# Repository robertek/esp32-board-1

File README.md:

# esp32-board-1
Simple ESP32 board design.

Features:
 * 1S lipo battery power
 * battery charger through microUSB
 * UART header for programming
 * I2C header for peripheral
 * battery monitoring throuh ADC

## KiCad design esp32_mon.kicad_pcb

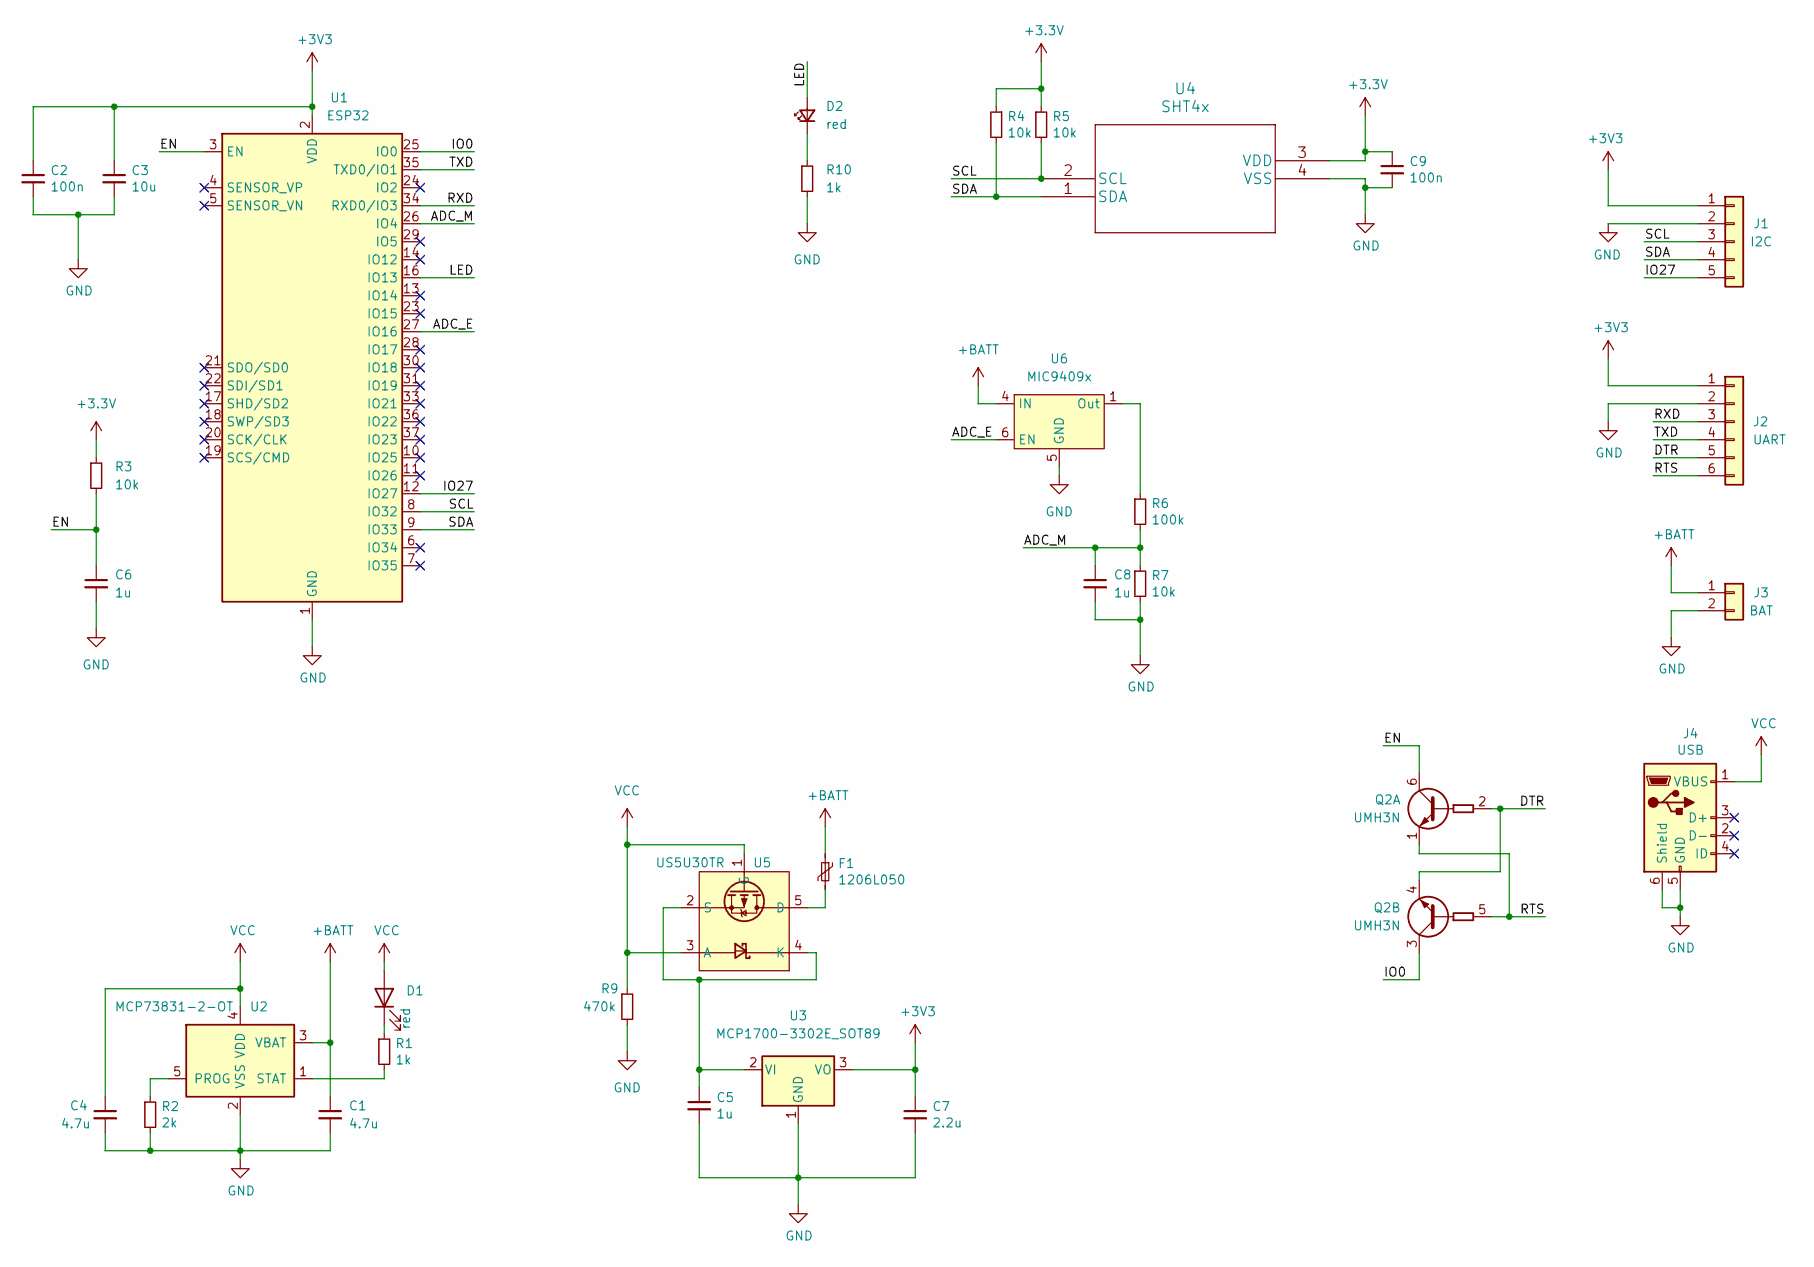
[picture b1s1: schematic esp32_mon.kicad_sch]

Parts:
C1, C4: 4.7u; C_0805_2012Metric_Pad1.18x1.45mm_HandSolder
C2, C9: 100n; C_0805_2012Metric_Pad1.18x1.45mm_HandSolder
C3: 10u; C_0805_2012Metric_Pad1.18x1.45mm_HandSolder
C5, C6, C8: 1u; C_0805_2012Metric_Pad1.18x1.45mm_HandSolder
C7: 2.2u; C_0805_2012Metric_Pad1.18x1.45mm_HandSolder
D1, D2: red; D_0805_2012Metric_Pad1.15x1.40mm_HandSolder
F1: 1206L050; Fuse_1206_3216Metric_Pad1.42x1.75mm_HandSolder
J1: I2C; PinHeader_1x05_P2.54mm_Vertical
J2: UART; PinSocket_1x06_P2.54mm_Horizontal
J3: BAT; JST_PH_S2B-PH-K_1x02_P2.00mm_Horizontal
J4: USB; USB_Micro-B_Amphenol_10104110_Horizontal
Q2: UMH3N; SOT-363_SC-70-6
R1, R10: 1k; R_0805_2012Metric_Pad1.20x1.40mm_HandSolder
R2: 2k; R_0805_2012Metric_Pad1.20x1.40mm_HandSolder
R3, R4, R5, R7: 10k; R_0805_2012Metric_Pad1.20x1.40mm_HandSolder
R6: 100k; R_0805_2012Metric_Pad1.20x1.40mm_HandSolder
R9: 470k; R_0805_2012Metric_Pad1.20x1.40mm_HandSolder
U1: ESP32; ESP32-WROOM-32
U2: MCP73831-2-OT; SOT-23-5
U3: MCP1700-3302E_SOT89; SOT-89-3
U4: SHT4x
U5: US5U30TR; SOT-353_SC-70-5
U6: MIC9409x; SOT-363_SC-70-6

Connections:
+BATT: C1.1, F1.1, J3.1, U2.3 (VBAT), U6.4 (IN)
/ADC_E: U1.27 (IO16), U6.6 (EN)
/ADC_M: C8.1, R6.2, R7.1, U1.26 (IO4)
/DTR: J2.5, Q2.2 (B1), Q2.4 (E2)
/EN: C6.1, Q2.6 (C1), R3.2, U1.3 (EN)
/IO0: Q2.3 (C2), U1.25 (IO0)
/IO27: J1.5, U1.12 (IO27)
/LED: D2.2 (A), U1.16 (IO13)
/RTS: J2.6, Q2.1 (E1), Q2.5 (B2)
/RXD: J2.3, U1.34 (RXD0/IO3)
/SCL: J1.3, R5.2, U1.8 (IO32), U4.2 (SCL)
/SDA: J1.4, R4.2, U1.9 (IO33), U4.1 (SDA)
/TXD: J2.4, U1.35 (TXD0/IO1)
GND: C1.2, C2.2, C3.2, C4.2, C5.2, C6.2, C7.2, C8.2, C9.2, J1.2, J2.2, J3.2, J4.5 (GND), J4.6 (Shield), R2.2, R7.2, R9.2, R10.2, U1.1 (GND), U1.15 (GND), U1.38 (GND), U1.39 (GND), U2.2 (VSS), U3.1 (GND), U4.4 (VSS), U6.2 (GND), U6.5 (GND)
unnamed: C5.1, U3.2 (VI), U5.2 (S), U5.4 (K)
unnamed: D1.1 (K), R1.1
unnamed: D2.1 (K), R10.1
unnamed: F1.2, U5.5 (D)
unnamed: R1.2, U2.1 (STAT)
unnamed: R2.1, U2.5 (PROG)
unnamed: R6.1, U6.1 (Out)
VCC: C4.1, D1.2 (A), J4.1 (VBUS), R9.1, U2.4 (VDD), U5.1 (G), U5.3 (A)

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
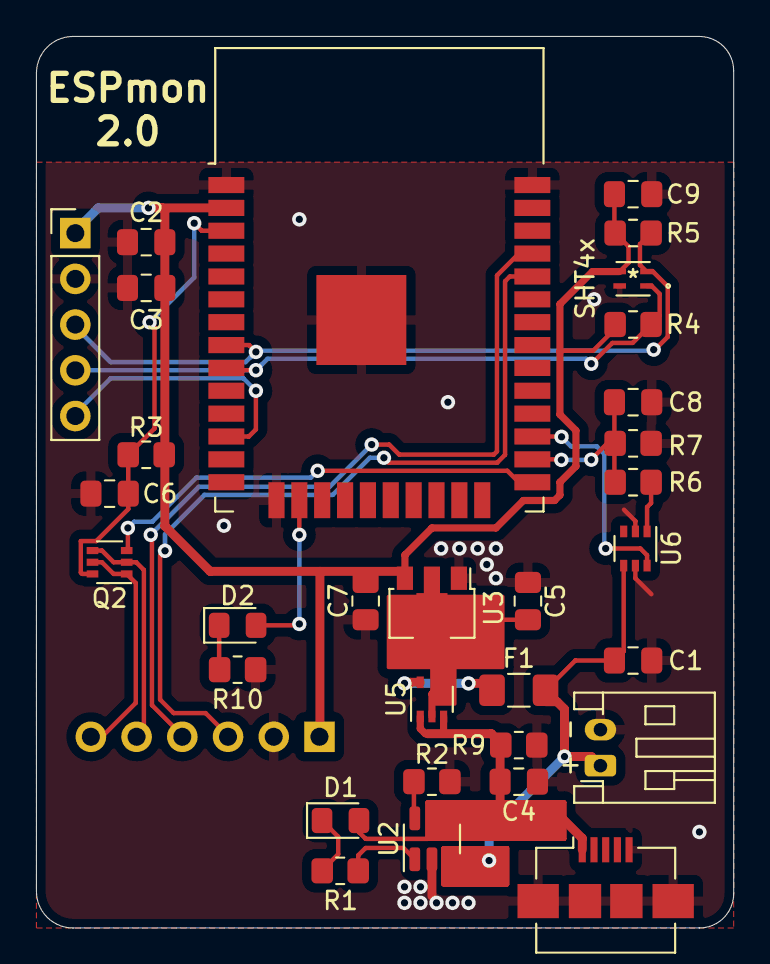
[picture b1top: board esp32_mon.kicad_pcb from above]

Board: 2 copper layers, 38.7 x 49.5 mm, 32 parts (1 on the bottom side), 23 nets.

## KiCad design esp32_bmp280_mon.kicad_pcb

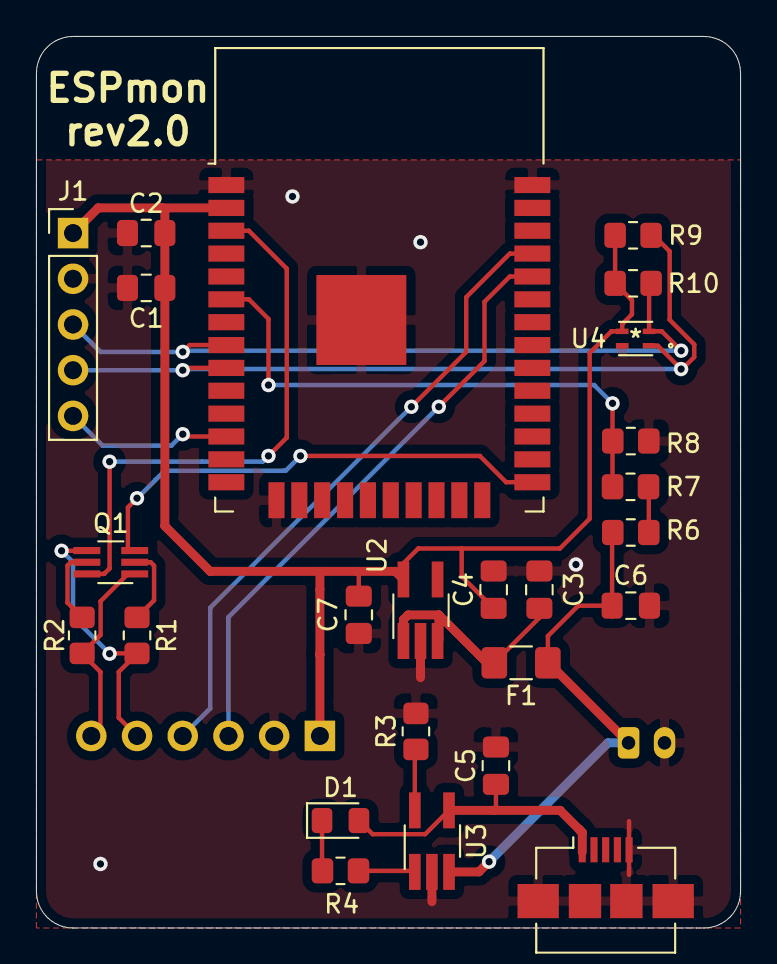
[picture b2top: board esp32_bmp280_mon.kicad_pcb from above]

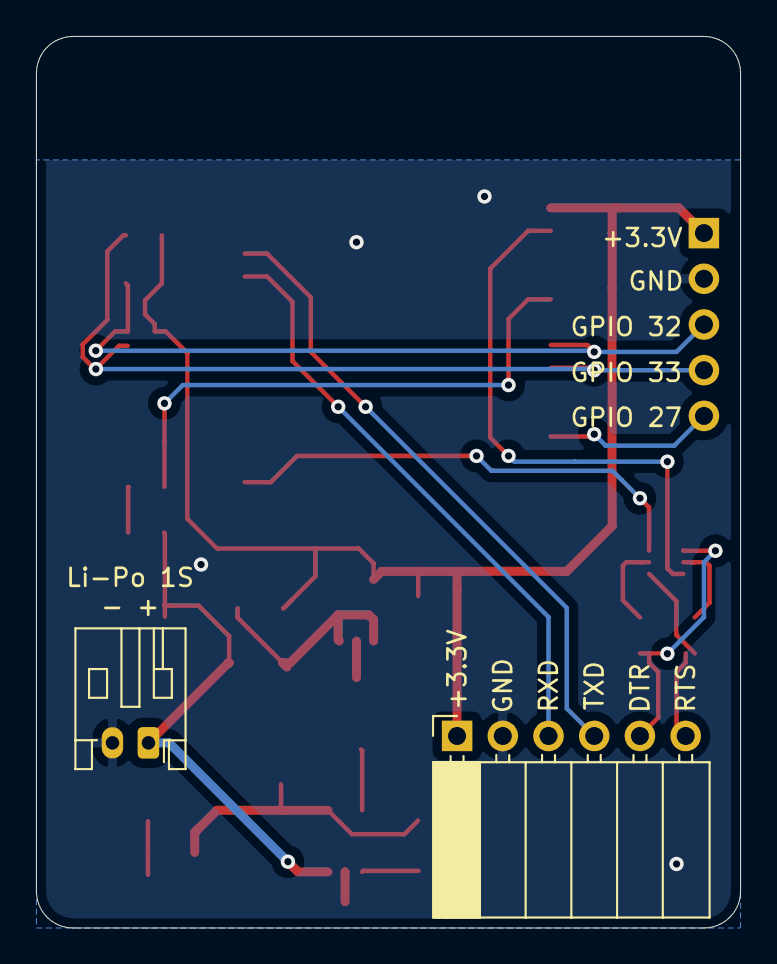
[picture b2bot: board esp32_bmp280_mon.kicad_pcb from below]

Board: 2 copper layers, 39.1 x 49.5 mm, 27 parts (2 on the bottom side), 21 nets.

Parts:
C1: 100nF; C_0805_2012Metric_Pad1.18x1.45mm_HandSolder
C2: 10uF; C_0805_2012Metric_Pad1.18x1.45mm_HandSolder
C3, C5, C6: 1uF; C_0805_2012Metric_Pad1.18x1.45mm_HandSolder
C4: 2.2uF; C_0805_2012Metric_Pad1.18x1.45mm_HandSolder
C7: 100n; C_0805_2012Metric_Pad1.18x1.45mm_HandSolder
D1: red; D_0805_2012Metric_Pad1.15x1.40mm_HandSolder
F1: 1206L050; Fuse_1206_3216Metric_Pad1.42x1.75mm_HandSolder
J1: I2C; PinHeader_1x05_P2.54mm_Vertical
J2: UART; PinSocket_1x06_P2.54mm_Horizontal
J3: BAT; JST_PH_S2B-PH-K_1x02_P2.00mm_Horizontal
J4: USB_B_Micro; USB_Micro-B_Amphenol_10104110_Horizontal
Q1: MMDT3904; SOT-363_SC-70-6_Handsoldering
R1, R2, R9, R10: 10k; R_0805_2012Metric_Pad1.20x1.40mm_HandSolder
R3: 2k; R_0805_2012Metric_Pad1.20x1.40mm_HandSolder
R4: 1k; R_0805_2012Metric_Pad1.20x1.40mm_HandSolder
R6, R7: 2m; R_0805_2012Metric_Pad1.20x1.40mm_HandSolder
R8: 1m; R_0805_2012Metric_Pad1.20x1.40mm_HandSolder
U1: ESP32-WROOM-32
U2: RT9080-33GJ5; TSOT-23-5_HandSoldering
U3: STC4054GR; TSOT-23-5_HandSoldering
U4: SHT40-AD1B-R2

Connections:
+3V3: C1.1, C2.1, C4.1, C7.1, J1.1, J2.1, R9.1, R10.1, U1.2, U2.5, U4.3
+BATT: C6.1, F1.1, J3.1, R6.1, U3.3
/DTR: J2.5, Q1.4, R1.2
/EN: Q1.6, U1.3
/IO0: Q1.3, U1.25
/IO27: J1.5, U1.12
/IO32: J1.3, R10.2, U1.8, U4.2
/IO33: J1.4, R9.2, U1.9, U4.1
/IO34: R7.2, R8.1, U1.6
/RTS: J2.6, Q1.1, R2.2
/RXD: J2.3, U1.34
/TXD: J2.4, U1.35
GND: C1.2, C2.2, C3.2, C4.2, C5.2, C6.2, C7.2, J1.2, J2.2, J3.2, J4.5, J4.6, R3.2, R8.2, U1.1, U1.15, U1.38, U1.39, U2.2, U3.2, U4.4
unnamed: C3.1, F1.2, U2.1, U2.3
unnamed: D1.1, R4.1
unnamed: Q1.2, R1.1
unnamed: Q1.5, R2.1
unnamed: R3.1, U3.5
unnamed: R4.2, U3.1
unnamed: R6.2, R7.1
VCC: C5.1, D1.2, J4.1, U3.4

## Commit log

2021-12-07 initial project files commit
2021-12-07 add LICENSE
2021-12-08 remove old libs and add RT9080 and STC4054
2021-12-13 port to SHT40 sensor on board and different LDO and charger
2022-01-04 update to Kicad 6 and various updates to design
2022-01-04 cleanup old project
2022-01-04 .gitignore: ignore backups
2022-01-04 minor cleanup
2022-02-13 update to availabe parts and tweaks
2022-02-28 esp32_mon.kicad_pcb: minor cleanup
2022-02-28 .gitignore: ignore .bak files

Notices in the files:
parts and their libraries:
Copyright 2021 Accelerated Designs. All rights reserved.
